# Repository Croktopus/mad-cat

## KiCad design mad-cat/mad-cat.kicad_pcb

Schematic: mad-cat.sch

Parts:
C1, C2, C3, C4, C9, C10, C11, C12, C13: 0.1u; C_0603_1608Metric
C5: 10u; C_0603_1608Metric
C6: 1u; C_0603_1608Metric
C7, C8: 22p; C_0603_1608Metric
D1, D2, D3, D4, D5, D6, D7, D8, D9, D10, D11, D12, D13, D14, D15, D16, D17, D18, D19, D20, D21, D22, D23, D24, D25, D26, D27, D28, D29, D30, D31, D32, D33, D34, D35, D36, D37, D38, D39, D40, D41, D42, D43, D44, D45, D46, D47, D48, D49, D50, D51, D52, D53, D54, D55, D56, D57, D58, D59, D60, D61, D62, D63, D64, D65, D66, D67, D68, D69, D70, D71, D72, D73, D74, D75, D76, D77, D78, D79, D80, D81, D82, D83, D84, D85, D86, D87, D88, D89, D90, D91, D92, D93, D94, D95, D96, D97: D; D_SOD-123
EC1, EC2: EC11E
ESD1: PRTR5V0U2X; SOT-143
H1, H2, H3, H4, H5, H6, H7, H8, H9, H10: MountingHole_Pad; m2.5_pad_via
J1: Conn_01x04; JST_SH_SM04B-SRSS-TB_1x04-1MP_P1.00mm_Horizontal
J2: Conn_02x03_Odd_Even; PinHeader_2x03_P2.54mm_Vertical
LED1: 3V 5mA; LED_0805_lightpipe
LOGO1: MountingHole; metamechs logo half
POT1: TC33X-2-103E; Trimpot_3.8mmx3.6mm_TC33X-2-103E; MPN TC33X-2-103E; Digi-Key_PN TC33X-103ETR-ND
PTC1: 500mA; Fuse_0805_2012Metric
R1, R2: 22; R_0603_1608Metric
R5: 510; R_0603_1608Metric
R6, R7, R8, R9, R10: 10K; R_0603_1608Metric
RST1: SW_PUSH; TS-1187A-B-A-B
SW0,0: ESC; MX_100
SW0,1: ESC/F1; MX_100
SW0,2: F1; MX_100
SW0,2-1, SW0,3: F2; MX_100
SW0,3-1, SW0,4: F3; MX_100
SW0,4-1, SW0,5: F4; MX_100
SW0,5-1, SW0,6: F5; MX_100
SW0,6-1, SW0,7: F6; MX_100
SW0,7-1, SW0,8: F7; MX_100
SW0,8-1, SW0,9: F8; MX_100
SW0,9-1, SW0,10: F9; MX_100
SW0,10-1, SW0,11: F10; MX_100
SW0,11-1, SW0,12: F11; MX_100
SW0,12-1: F12; MX_100
SW0,13: F12/PRT; MX_100
SW0,14: INS; MX_100
SW0,15, SW1,15-1: HOME; MX_100
SW0,16, SW1,16-1: PGUP; MX_100
SW1,0, SW1,0-1: PF1; MX_100
SW1,1: TILDE; MX_100
SW1,2: 1; MX_100
SW1,3: 2; MX_100
SW1,4: 3; MX_100
SW1,5: 4; MX_100
SW1,6: 5; MX_100
SW1,7: 6; MX_100
SW1,8: 7; MX_100
SW1,9: 8; MX_100
SW1,10: 9; MX_100
SW1,11: 0; MX_100
SW1,12: -; MX_100
SW1,13: =; MX_100
SW1,14: BACKSPACE; MX_200
SW1,14-1: S_BS_L; MX_100_lpin
SW1,15: END; MX_100
SW1,16: PGDN; MX_100
SW2,0, SW2,0-1: PF2; MX_100
SW2,1: TAB; MX_150
SW2,2: Q; MX_100
SW2,3: W; MX_100
SW2,4: E; MX_100
SW2,5: R; MX_100
SW2,6: T; MX_100
SW2,7: Y; MX_100
SW2,8: U; MX_100
SW2,9: I; MX_100
SW2,10: O; MX_100
SW2,11: P; MX_100
SW2,12: [; MX_100
SW2,13: ]; MX_100
SW2,14: \\; MX_150
SW2,15: S_BS_R; MX_100_rpin
SW2,16: PRT; MX_100
SW3,0, SW3,0-1: PF3; MX_100
SW3,1: CAPS; MX_175
SW3,1-1: ST_CAPS; MX_125
SW3,2: A; MX_100
SW3,3: S; MX_100
SW3,4: D; MX_100
SW3,5: F; MX_100
SW3,6: G; MX_100
SW3,7: H; MX_100
SW3,8: J; MX_100
SW3,9: K; MX_100
SW3,10: L; MX_100
SW3,11: COLONS; MX_100
SW3,12: QUOTE; MX_100
SW3,13: ISO_#; MX_100
SW3,14: ENT; MX_225_stabflip
SW3,14-1: ISO_ENT; MX_ISO_stabflip
SW3,15: DEL; MX_200
SW3,15-1: DEL; MX_200_stabflip
SW3,15-2, SW3,15-3: DEL; MX_100
SW3,16, SW5,16-1: NP_ENT; MX_200
SW3,16-1: 1U_ENT; MX_100
SW4,0, SW4,0-1: PF4; MX_100
SW4,1: L_SHIFT; MX_225
SW4,1-1: ISO_SHIFT; MX_125_lpin
SW4,2: ISO_\\; MX_100
SW4,3: Z; MX_100
SW4,4: X; MX_100
SW4,5: C; MX_100
SW4,6: V; MX_100
SW4,7: B; MX_100
SW4,8: N; MX_100
SW4,9: M; MX_100
SW4,10: COMMA; MX_100
SW4,11: DOT; MX_100
SW4,12: /; MX_100
SW4,13: S_SHIFT; MX_175_labeled
SW4,13-1: R_SHIFT; MX_275_stabflip_labeled
SW4,14, SW5,0-1: FN; MX_100
SW4,14-1, SW4,16: UP; MX_100
SW4,15, SW4,15-1: Extra 1u; MX_100
SW4,16-1: extra_1u; MX_100
SW5,0: PF5; MX_100
SW5,1, SW5,11-1: CTRL; MX_150_labeled
SW5,1-1: CTRL; MX_125_labeled
SW5,2, SW5,11: WIN; MX_100_labeled
SW5,2-1: WIN; MX_125_labeled
SW5,3: ALT; MX_150_labeled
SW5,3-1: ALT; MX_125_labeled
SW5,7: 6.25U; MX_625_stabflip
SW5,7-1: 6U; MX_600_stabflip_3
SW5,10: ALT; MX_150
SW5,12: CTRL; MX_150
SW5,12-1: LEFT; MX_100
SW5,13: LEFT/DOWN; MX_100
SW5,14: DOWN/RIGHT; MX_100
SW5,15: 1u; MX_100
SW5,16: RIGHT; MX_100
SW5,16-2: 1u_ent; MX_100
U1: ATMEGA32U4; TQFP-44_10x10mm_P0.8mm
Y1: 16M; Crystal_SMD_SeikoEpson_TSX3225-4Pin_3.2x2.5mm

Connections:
/D+: ESD1.2, J1.2, R2.2
/D-: ESD1.3, J1.3, R1.2
/RES: J2.5, R6.1, RST1.2, U1.13 (~RESET)
/c0: EC1.S1, J2.4, SW0,0.2, SW1,0.2, SW1,0-1.2, SW2,0.2, SW2,0-1.2, SW3,0.2, SW3,0-1.2, SW4,0.2, SW4,0-1.2, SW5,0.2, SW5,0-1.2, U1.10 (PB2/MOSI)
/c1: J2.1, SW0,1.2, SW1,1.2, SW2,1.2, SW3,1.2, SW3,1-1.1, SW4,1.2, SW4,1-1.2, SW5,1.2, SW5,1-1.2, U1.11 (PB3/MISO)
/c2: SW0,2.2, SW0,2-1.1, SW1,2.2, SW2,2.2, SW3,2.2, SW4,2.2, SW5,2.2, SW5,2-1.2, U1.12 (PB7/~RTS)
/c3: SW0,3.2, SW0,3-1.1, SW1,3.2, SW2,3.2, SW3,3.2, SW4,3.2, SW5,3.2, SW5,3-1.2, U1.18 (PD0/INT0)
/c4: SW0,4.2, SW0,4-1.1, SW1,4.2, SW2,4.2, SW3,4.2, SW4,4.2, U1.19 (PD1/INT1)
/c5: SW0,5.2, SW0,5-1.2, SW1,5.2, SW2,5.2, SW3,5.2, SW4,5.2, U1.20 (PD2/RXD1)
/c6: SW0,6.2, SW0,6-1.1, SW1,6.2, SW2,6.2, SW3,6.2, SW4,6.2, U1.29 (PB5)
/c7: SW0,7.2, SW0,7-1.1, SW1,7.2, SW2,7.2, SW3,7.2, SW4,7.2, SW5,7.2, SW5,7-1.2, U1.30 (PB6)
/c8: SW0,8.2, SW0,8-1.1, SW1,8.2, SW2,8.2, SW3,8.2, SW4,8.2, U1.31 (PC6)
/c9: SW0,9.2, SW0,9-1.2, SW1,9.2, SW2,9.2, SW3,9.2, SW4,9.2, U1.32 (PC7)
/c10: SW0,10.2, SW0,10-1.1, SW1,10.2, SW2,10.2, SW3,10.2, SW4,10.2, SW5,10.2, U1.36 (PF7)
/c11: SW0,11.2, SW0,11-1.1, SW1,11.2, SW2,11.2, SW3,11.2, SW4,11.2, SW5,11.2, SW5,11-1.2, U1.37 (PF6)
/c12: SW0,12.2, SW0,12-1.1, SW1,12.2, SW2,12.2, SW3,12.2, SW4,12.2, SW5,12.2, SW5,12-1.2, U1.38 (PF5)
/c13: SW0,13.2, SW1,13.2, SW2,13.2, SW3,13.2, SW4,13.2, SW4,13-1.2, SW5,13.2, U1.39 (PF4)
/c14: SW0,14.2, SW1,14.2, SW1,14-1.2, SW2,14.2, SW3,14.2, SW3,14-1.2, SW4,14.2, SW4,14-1.2, SW5,14.2, U1.40 (PF1)
/c15: SW0,15.2, SW1,15.2, SW1,15-1.2, SW2,15.2, SW3,15.2, SW3,15-1.2, SW3,15-2.2, SW3,15-3.2, SW4,15.2, SW4,15-1.2, SW5,15.2, U1.41 (PF0)
/c16: EC2.S1, SW0,16.2, SW1,16.2, SW1,16-1.2, SW2,16.2, SW3,16.2, SW3,16-1.2, SW4,16.2, SW4,16-1.2, SW5,16.2, SW5,16-1.2, SW5,16-2.2, U1.1 (PE6/AIN0)
/enc+: C10.1, C13.1, J2.3, R7.2, R10.2, U1.9 (PB1/SCK)
/enc-: C11.2, C12.2, R8.1, R9.1, U1.8 (PB0/SS)
/r0: D1.1, D2.1, D3.1, D4.1, D5.1, D6.1, D7.1, D8.1, D9.1, D10.1, D11.1, D12.1, D13.1, D14.1, D15.1, D16.1, D17.1, U1.22 (PD5/XCK1)
/r1: D18.1, D19.1, D20.1, D21.1, D22.1, D23.1, D24.1, D25.1, D26.1, D27.1, D28.1, D29.1, D30.1, D31.1, D32.1, D33.1, D34.1, U1.21 (PD3/TXD1)
/r2: D35.1, D36.1, D37.1, D38.1, D39.1, D40.1, D41.1, D42.1, D43.1, D44.1, D45.1, D46.1, D47.1, D48.1, D49.1, D50.1, D51.1, U1.25 (ICP1/PD4)
/r3: D52.1, D53.1, D54.1, D55.1, D56.1, D57.1, D58.1, D59.1, D60.1, D61.1, D62.1, D63.1, D64.1, D65.1, D66.1, D67.1, D68.1, U1.26 (T1/PD6)
/r4: D69.1, D70.1, D71.1, D72.1, D73.1, D74.1, D75.1, D76.1, D77.1, D78.1, D79.1, D80.1, D81.1, D82.1, D83.1, D84.1, D85.1, U1.27 (T0/PD7)
/r5: D86.1, D87.1, D88.1, D89.1, D90.1, D91.1, D92.1, D93.1, D94.1, D95.1, D96.1, D97.1, U1.28 (PB4)
/rd+: R2.1, U1.4 (D+)
/rd-: R1.1, U1.3 (D-)
GND: C1.2, C2.2, C3.2, C4.2, C5.2, C6.2, C7.2, C8.2, C9.2, C10.2, C11.1, C12.1, C13.2, EC1.C, EC2.C, ESD1.1, H1.1, H2.1, H3.1, H4.1, H5.1, H6.1, H7.1, H8.1, H9.1, H10.1, J1.1, J2.6, LED1.1, RST1.1, U1.5 (UGnd), U1.15 (GND), U1.23 (GND), U1.35 (GND), U1.43 (GND), Y1.2, Y1.4
unnamed: C6.1, U1.6 (UCap)
unnamed: C7.1, U1.16 (XTAL1), Y1.1
unnamed: C8.1, U1.17 (XTAL2), Y1.3
unnamed: C9.1, U1.42 (AREF)
unnamed: D1.2, EC1.S2, SW0,0.1
unnamed: D2.2, SW0,1.1
unnamed: D3.2, SW0,2.1, SW0,2-1.2
unnamed: D4.2, SW0,3.1, SW0,3-1.2
unnamed: D5.2, SW0,4.1, SW0,4-1.2
unnamed: D6.2, SW0,5.1, SW0,5-1.1
unnamed: D7.2, SW0,6.1, SW0,6-1.2
unnamed: D8.2, SW0,7.1, SW0,7-1.2
unnamed: D9.2, SW0,8.1, SW0,8-1.2
unnamed: D10.2, SW0,9.1, SW0,9-1.1
unnamed: D11.2, SW0,10.1, SW0,10-1.2
unnamed: D12.2, SW0,11.1, SW0,11-1.2
unnamed: D13.2, SW0,12.1, SW0,12-1.2
unnamed: D14.2, SW0,13.1
unnamed: D15.2, SW0,14.1
unnamed: D16.2, SW0,15.1
unnamed: D17.2, SW0,16.1
unnamed: D18.2, SW1,0.1, SW1,0-1.1
unnamed: D19.2, SW1,1.1
unnamed: D20.2, SW1,2.1
unnamed: D21.2, SW1,3.1
unnamed: D22.2, SW1,4.1
unnamed: D23.2, SW1,5.1
unnamed: D24.2, SW1,6.1
unnamed: D25.2, SW1,7.1
unnamed: D26.2, SW1,8.1
unnamed: D27.2, SW1,9.1
unnamed: D28.2, SW1,10.1
unnamed: D29.2, SW1,11.1
unnamed: D30.2, SW1,12.1
unnamed: D31.2, SW1,13.1
unnamed: D32.2, SW1,14.1, SW1,14-1.1
unnamed: D33.2, SW1,15.1, SW1,15-1.1
unnamed: D34.2, SW1,16.1, SW1,16-1.1
unnamed: D35.2, SW2,0.1, SW2,0-1.1
unnamed: D36.2, SW2,1.1
unnamed: D37.2, SW2,2.1
unnamed: D38.2, SW2,3.1
unnamed: D39.2, SW2,4.1
unnamed: D40.2, SW2,5.1
unnamed: D41.2, SW2,6.1
unnamed: D42.2, SW2,7.1
unnamed: D43.2, SW2,8.1
unnamed: D44.2, SW2,9.1
unnamed: D45.2, SW2,10.1
unnamed: D46.2, SW2,11.1
unnamed: D47.2, SW2,12.1
unnamed: D48.2, SW2,13.1
unnamed: D49.2, SW2,14.1
unnamed: D50.2, SW2,15.1
unnamed: D51.2, EC2.S2, SW2,16.1
unnamed: D52.2, SW3,0.1, SW3,0-1.1
unnamed: D53.2, SW3,1.1, SW3,1-1.2
unnamed: D54.2, SW3,2.1
unnamed: D55.2, SW3,3.1
unnamed: D56.2, SW3,4.1
unnamed: D57.2, SW3,5.1
unnamed: D58.2, SW3,6.1
unnamed: D59.2, SW3,7.1
unnamed: D60.2, SW3,8.1
unnamed: D61.2, SW3,9.1
unnamed: D62.2, SW3,10.1
unnamed: D63.2, SW3,11.1
unnamed: D64.2, SW3,12.1
unnamed: D65.2, SW3,13.1
unnamed: D66.2, SW3,14.1, SW3,14-1.1
unnamed: D67.2, SW3,15.1, SW3,15-1.1, SW3,15-2.1, SW3,15-3.1
unnamed: D68.2, SW3,16.1, SW3,16-1.1
unnamed: D69.2, SW4,0.1, SW4,0-1.1
unnamed: D70.2, SW4,1.1, SW4,1-1.1
unnamed: D71.2, SW4,2.1
unnamed: D72.2, SW4,3.1
unnamed: D73.2, SW4,4.1
unnamed: D74.2, SW4,5.1
unnamed: D75.2, SW4,6.1
unnamed: D76.2, SW4,7.1
unnamed: D77.2, SW4,8.1
unnamed: D78.2, SW4,9.1
unnamed: D79.2, SW4,10.1
unnamed: D80.2, SW4,11.1
unnamed: D81.2, SW4,12.1
unnamed: D82.2, SW4,13.1, SW4,13-1.1
unnamed: D83.2, SW4,14.1, SW4,14-1.1
unnamed: D84.2, SW4,15.1, SW4,15-1.1
unnamed: D85.2, SW4,16.1, SW4,16-1.1
unnamed: D86.2, SW5,0.1, SW5,0-1.1
unnamed: D87.2, SW5,1.1, SW5,1-1.1
unnamed: D88.2, SW5,2.1, SW5,2-1.1
unnamed: D89.2, SW5,3.1, SW5,3-1.1
unnamed: D90.2, SW5,7.1, SW5,7-1.1
unnamed: D91.2, SW5,10.1
unnamed: D92.2, SW5,11.1, SW5,11-1.1
unnamed: D93.2, SW5,12.1, SW5,12-1.1
unnamed: D94.2, SW5,13.1
unnamed: D95.2, SW5,14.1
unnamed: D96.2, SW5,15.1
unnamed: D97.2, SW5,16.1, SW5,16-1.1, SW5,16-2.1
unnamed: EC1.A, R7.1
unnamed: EC1.B, R8.2
unnamed: EC2.A, R10.1
unnamed: EC2.B, R9.2
unnamed: LED1.2, POT1.1, POT1.2
unnamed: POT1.3, R5.1
unnamed: R5.2, U1.33 (~HWB/PE2)
VCC: C1.1, C2.1, C3.1, C4.1, C5.1, J2.2, PTC1.2, R6.2, U1.2 (UVcc), U1.7 (VBus), U1.14 (VCC), U1.24 (AVCC), U1.34 (VCC), U1.44 (AVCC)
vbus: ESD1.4, J1.4, PTC1.1

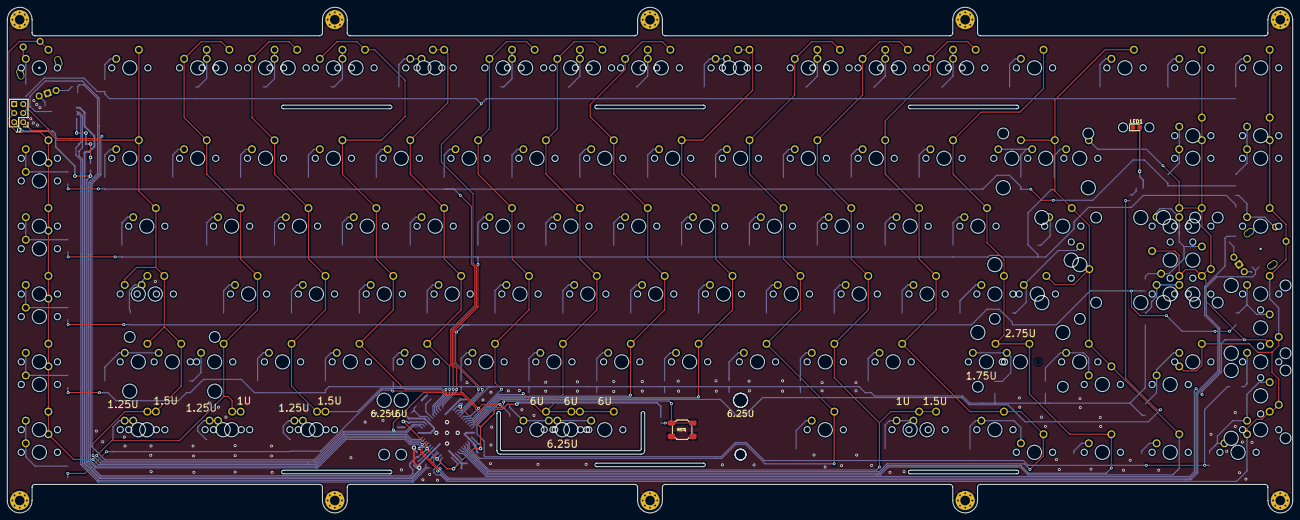
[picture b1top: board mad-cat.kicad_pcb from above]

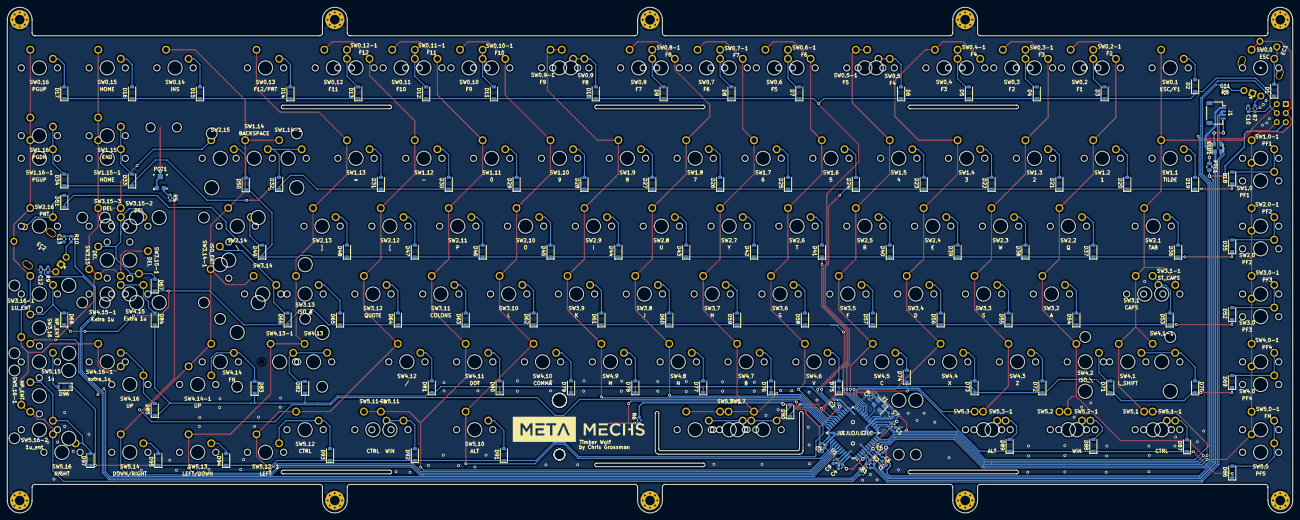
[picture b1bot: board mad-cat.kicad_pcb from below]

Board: 2 copper layers, 360.9 x 142.0 mm, 275 parts (125 on the bottom side), 141 nets.

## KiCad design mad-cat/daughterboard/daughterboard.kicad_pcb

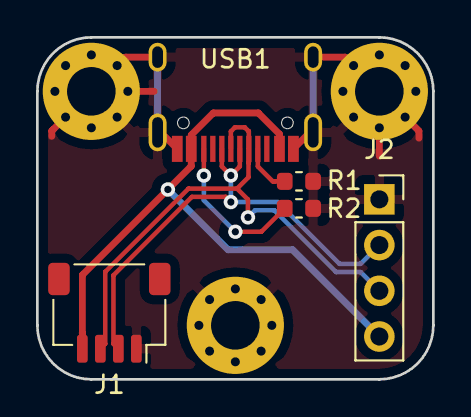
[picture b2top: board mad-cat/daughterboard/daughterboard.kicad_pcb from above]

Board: 2 copper layers, 22.0 x 19.0 mm, 8 parts (0 on the bottom side), 6 nets.

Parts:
H1, H2, H3: MountingHole_Pad; m2.5_pad_via
J1: Conn_01x04; JST_SH_SM04B-SRSS-TB_1x04-1MP_P1.00mm_Horizontal
J2: Conn_01x04; PinSocket_1x04_P2.54mm_Vertical
R1, R2: 5.1K; R_0603_1608Metric
USB1: HRO-TYPE-C-31-M-12; HRO-TYPE-C-31-M-12-Assembly

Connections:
/d+: J1.2, J2.2, USB1.6, USB1.8
/d-: J1.3, J2.3, USB1.5, USB1.7
/vbus: J1.4, J2.4, USB1.2, USB1.11
GND: H1.1, H2.1, H3.1, J1.1, J2.1, R1.1, R2.1, USB1.1, USB1.12, USB1.13
unnamed: R1.2, USB1.4
unnamed: R2.2, USB1.10

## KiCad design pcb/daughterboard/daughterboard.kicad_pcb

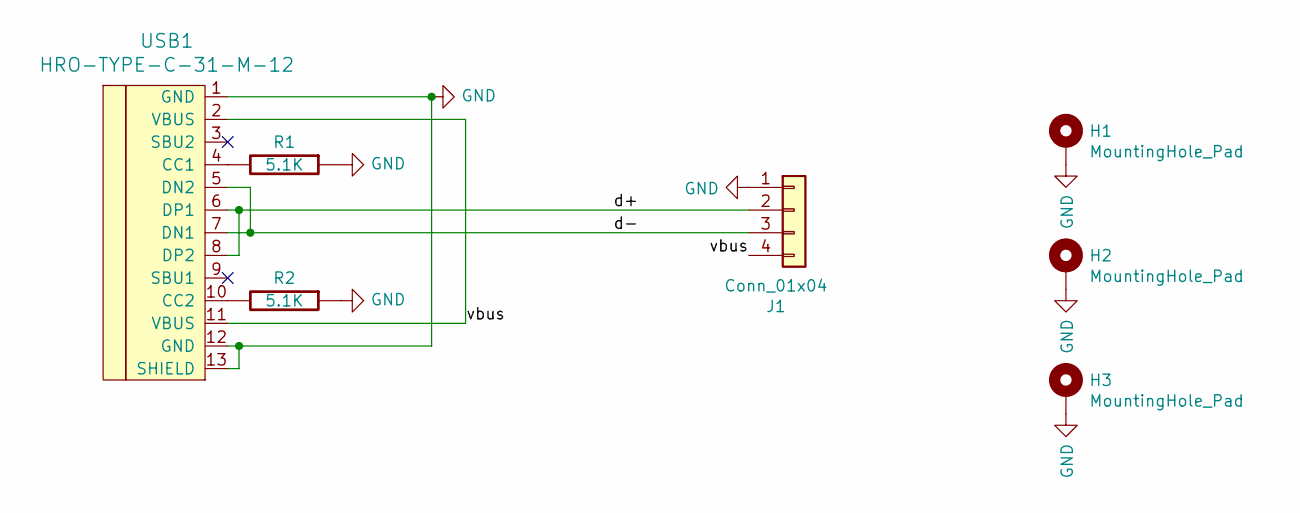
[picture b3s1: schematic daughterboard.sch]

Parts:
H1, H2, H3: MountingHole_Pad; m2.5_pad_via
J1: Conn_01x04; JST_SH_SM04B-SRSS-TB_1x04-1MP_P1.00mm_Horizontal
R1, R2: 5.1K; R_0603_1608Metric
USB1: HRO-TYPE-C-31-M-12; HRO-TYPE-C-31-M-12-Assembly

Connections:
/d+: J1.2, USB1.6 (DP1), USB1.8 (DP2)
/d-: J1.3, USB1.5 (DN2), USB1.7 (DN1)
/vbus: J1.4, USB1.2 (VBUS), USB1.11 (VBUS)
GND: H1.1, H2.1, H3.1, J1.1, R1.1, R2.1, USB1.1 (GND), USB1.12 (GND), USB1.13 (SHIELD)
unnamed: R1.2, USB1.4 (CC1)
unnamed: R2.2, USB1.10 (CC2)

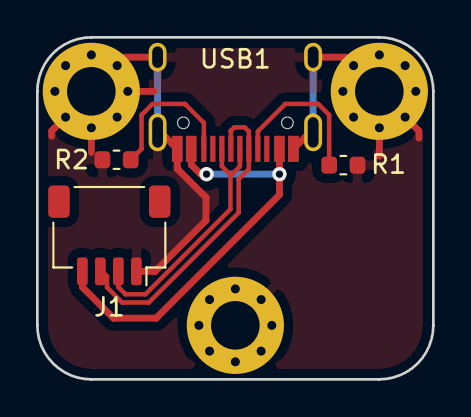
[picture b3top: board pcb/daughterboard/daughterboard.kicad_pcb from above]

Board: 2 copper layers, 22.0 x 19.0 mm, 7 parts (0 on the bottom side), 6 nets.

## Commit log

2019-05-07 pretty much finished the pcb
2019-05-07 exported step
2019-05-07 renaming
2019-05-09 adding flex cuts
2019-05-11 updating pcb cuts
2019-05-13 rebuilding pcb, adding switches to schematic
2019-05-14 "finished" traces
2019-05-15 even more compat, generating gerbers
2019-05-15 editing flex cuts
2019-05-20 Updating a lot
2019-05-20 new flex cuts
2019-05-22 redoing in mx only, adding trimpot for led
2019-05-22 fixed silk, created gerbers
2019-05-23 via stitching lol
2019-05-23 reverting vias
2019-05-23 added support for 2 1us on del
2019-05-23 little updates
2019-05-24 changed holes to m2.5
2019-05-24 ok maybe final but probably not
2019-05-25 redid daughterboard
2019-05-25 minor update
2019-05-27 spacebar labels
2019-05-29 via stitch, proto diode footprint
2019-05-29 gerbers
2019-05-29 rremoved vias around logo
2019-06-12 sent red proto to jlc
2019-06-14 redo layout after ic
2019-06-15 progress on redo
2019-06-15 via stitched proto
2019-06-15 design done for proto
2019-06-16 small updates
2019-06-22 back to editing pcb
2019-06-22 Update fp-info-cache
2019-06-24 added panel mount footprints
2019-06-25 proto ready
2019-06-25 zipped gerbers
2019-06-26 daughterboard updates
2019-06-29 added gnd vias
2019-06-29 getting ready to proto...again
2019-06-30 smol updates
2019-06-30 printing
2019-07-01 new gerbers
2019-07-06 updated switch rotations
2019-07-08 added logo, finalized? pcb
2019-08-13 slight edits
2019-08-14 new model
2019-12-10 starting on pre production
2019-12-15 prepared for pcba
2019-12-18 pcba files
2019-12-24 edited LED circuit, flipped stabs
2020-01-07 new edge cuts
2020-01-18 tweaked tracks
2020-04-11 switching to desktop
